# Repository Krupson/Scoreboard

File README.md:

# Scoreboard
An open-sourced project of digital 3D-printed scoreboard based on ESP32C6 and some WS2812 LEDs.

## Features
- Configurable colors and brightness
- Current state memory (score does not reset on power loss)
- Debounced buttons (prevents accidental add/subtract score 2nd time in very short period)
- Remote control over WiFi (Work in progress)

## Controls
### Control score
Click Tx_ADD and Tx_SUB buttons once to control score for choosen team.

### Switch sides
Double click SWITCH_SIDES button to switch sides of team 1 and team 2.

### Reset score
Double click RESET_SCORE.

## Config mode
In order to enter config mode long press SWITCH_SIDES button. While in config mode there will be "0000" displayed on the board. In order to exit config mode (and save new settings) long press SWITCH_SIDES again.

### Change brightness
While in config mode you can press and hold T1_ADD / T1_SUB buttons to increase or decrease brightness of the display.

### Change team color
While in config mode you can press Tx_ADD / Tx_SUB to change color for choosen team. Red and green should be the least power-hungry :)

## Roadmap
This project was started as something intended for our internal use. Since I am designing 3D models for this project in Fusion360 and I am beginner with this software - quality of the project is much less than acceptable. Honestly I think that the whole 3D model part needs to be recreated from scratch with use of components, project variables for some dimensions etc. 

In near future I am planning to export all STLs I have right now and create Bambu Studio project with all the parts needed to be printed split into buildplates. Then I would like to focus on firmware part, create new PCB design with its own battery and charging module (currently we use old powerbank for providing power to the device).

### Things to be done
#### General
- Create docs with parts needed to build the scoreboard
- Cleanup repo

#### 3D models
- Recreate from scratch

#### Firmware
- Get rid of Arduino project, move everything to PlatformIO project
- Review RTOS code
- Finish remote control server
- Create remote control client firmware
- Add support for temperature and humidity sensors
- Add support for SD card logging (score + temp + hum over time)

#### PCB
- Add temperture and humidity sensor
- Add SD card slot
- Add support for battery

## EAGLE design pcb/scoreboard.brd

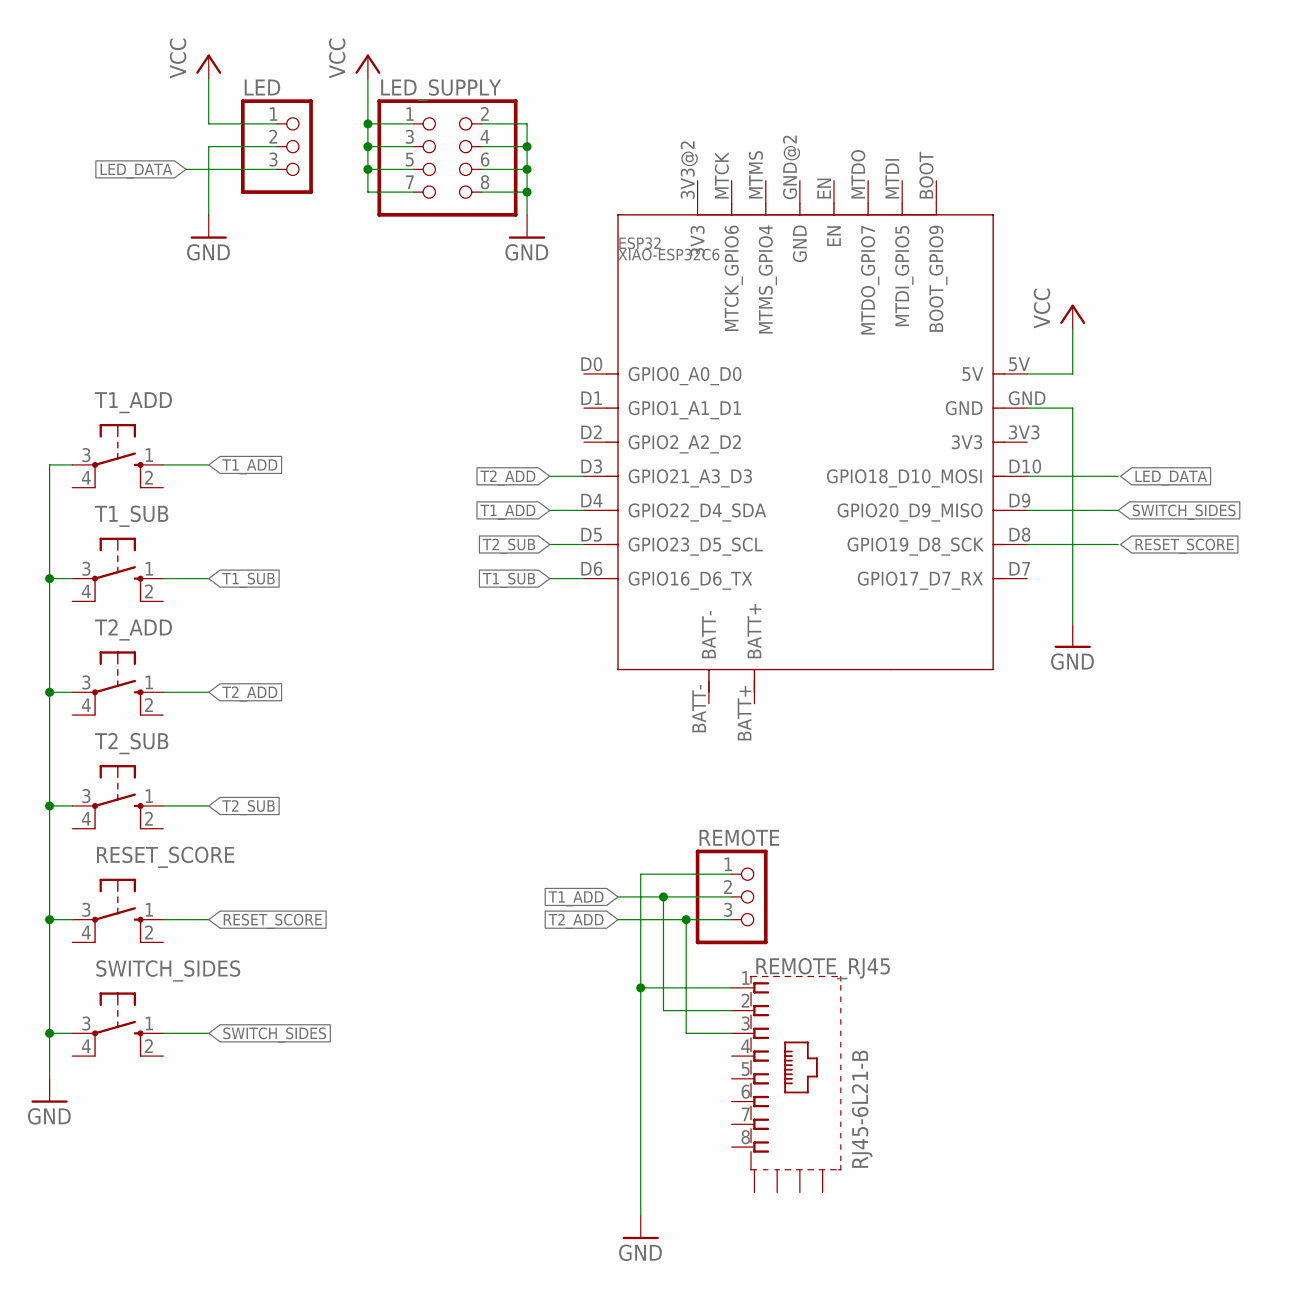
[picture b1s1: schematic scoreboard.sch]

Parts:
ESP32: XIAO-ESP32C6; XIAO-ESP32C6-MODULE14P-2.54-21X17.8MM
LED: PINHD-1X3; 1X03
LED_SUPPLY: PINHD-2X4; 2X04
REMOTE: PINHD-1X3; 1X03
REMOTE_RJ45: RJ45-6L21-B; RJ45-SHIELD1
RESET_SCORE: 10-XX; B3F-10XX
SWITCH_SIDES: 10-XX; B3F-10XX
T1_ADD, T1_SUB, T2_ADD, T2_SUB: 10-XX; B3F-10XX

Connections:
GND: ESP32.GND, LED.2, LED_SUPPLY.2, LED_SUPPLY.4, LED_SUPPLY.6, LED_SUPPLY.8, REMOTE.1, REMOTE_RJ45.1, RESET_SCORE.3, SWITCH_SIDES.3, T1_ADD.3, T1_SUB.3, T2_ADD.3, T2_SUB.3
LED_DATA: ESP32.D10 (GPIO18_D10_MOSI), LED.3
RESET_SCORE: ESP32.D8 (GPIO19_D8_SCK), RESET_SCORE.1 (S)
SWITCH_SIDES: ESP32.D9 (GPIO20_D9_MISO), SWITCH_SIDES.1 (S)
T1_ADD: ESP32.D4 (GPIO22_D4_SDA), REMOTE.2, REMOTE_RJ45.2, T1_ADD.1 (S)
T1_SUB: ESP32.D6 (GPIO16_D6_TX), T1_SUB.1 (S)
T2_ADD: ESP32.D3 (GPIO21_A3_D3), REMOTE.3, REMOTE_RJ45.3, T2_ADD.1 (S)
T2_SUB: ESP32.D5 (GPIO23_D5_SCL), T2_SUB.1 (S)
VCC: ESP32.5V, LED.1, LED_SUPPLY.1, LED_SUPPLY.3, LED_SUPPLY.5, LED_SUPPLY.7

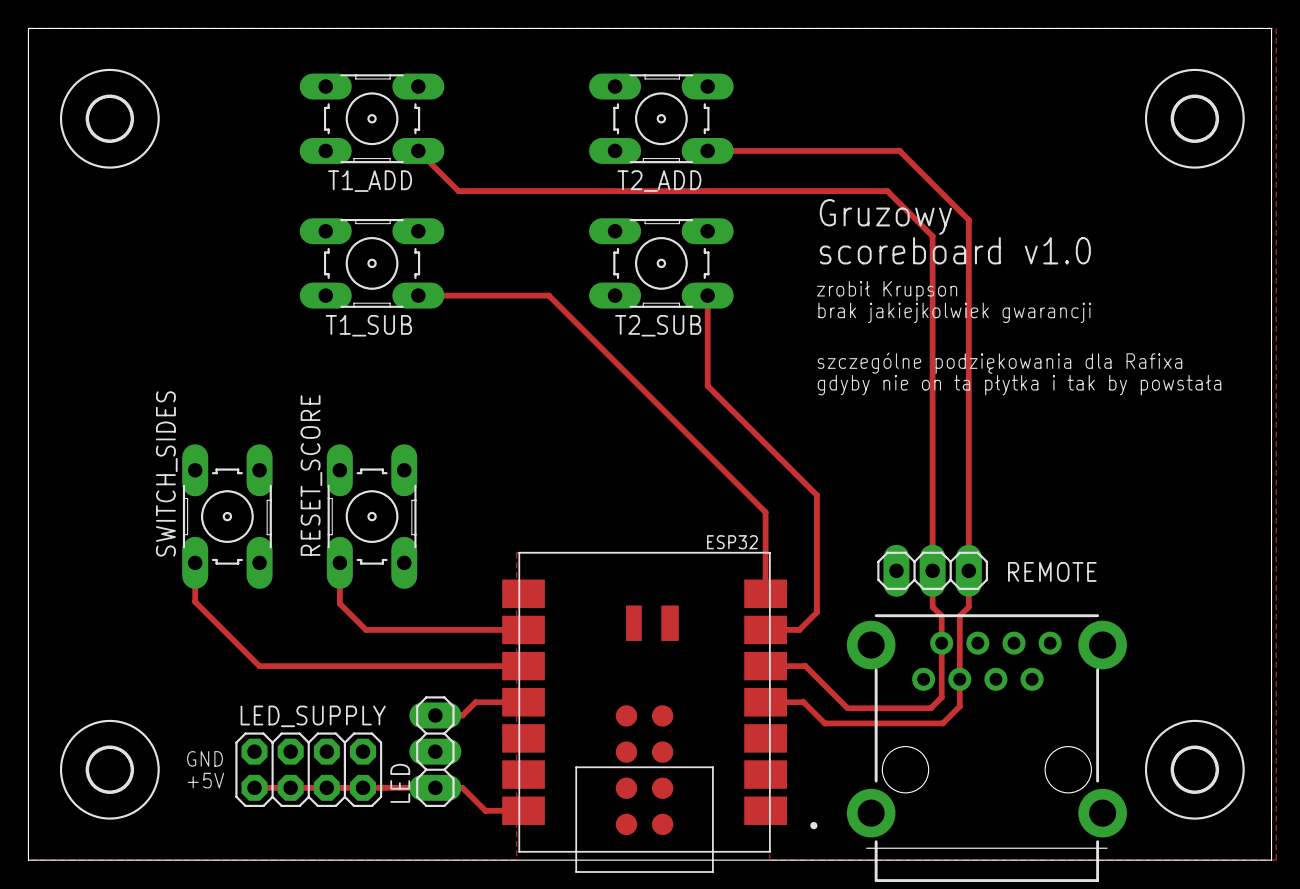
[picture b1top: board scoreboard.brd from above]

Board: 2 copper layers, 87.3 x 58.4 mm, 15 parts (0 on the bottom side), 9 nets.

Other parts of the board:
U$1, U$2, U$3, U$4: 3,0

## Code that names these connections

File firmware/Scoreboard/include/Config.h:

#pragma once

// Serial
#define SERIAL_BAUD_RATE        115200

// Network
#define WIFI_CONNECT_TIMEOUT_MS 10000
#define SERVER_PORT             80
#define WIFI_SSID               "GruzowyScoreboard"
#define WIFI_PASSWORD           "GRUZ2137"

// Scoreboard hardware
#define PIN_DATA          D10
#define PIN_T1_ADD        D4
#define PIN_T1_SUB        D6
#define PIN_T2_ADD        D3
#define PIN_T2_SUB        D5
#define PIN_RESET_SCORE   D8
#define PIN_SWITCH_SIDES  D9

// Scoreboard LEDs
#define LEDS_PER_SEGMENT                    4
#define LEDS_PER_DIGIT                      (LEDS_PER_SEGMENT * 7)
#define NUM_LEDS                            (LEDS_PER_DIGIT * 4)

// Scoreboard timing
#define MIN_SCORE_CHANGE_TIME_MS            500UL
#define MIN_BRIGHTNESS_CHANGE_TIME_MS       20UL

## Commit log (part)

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2026-05-09 Extract scoreboard code to separate class
2026-05-09 Remove some test files
2026-05-09 Move constants to Config.h
